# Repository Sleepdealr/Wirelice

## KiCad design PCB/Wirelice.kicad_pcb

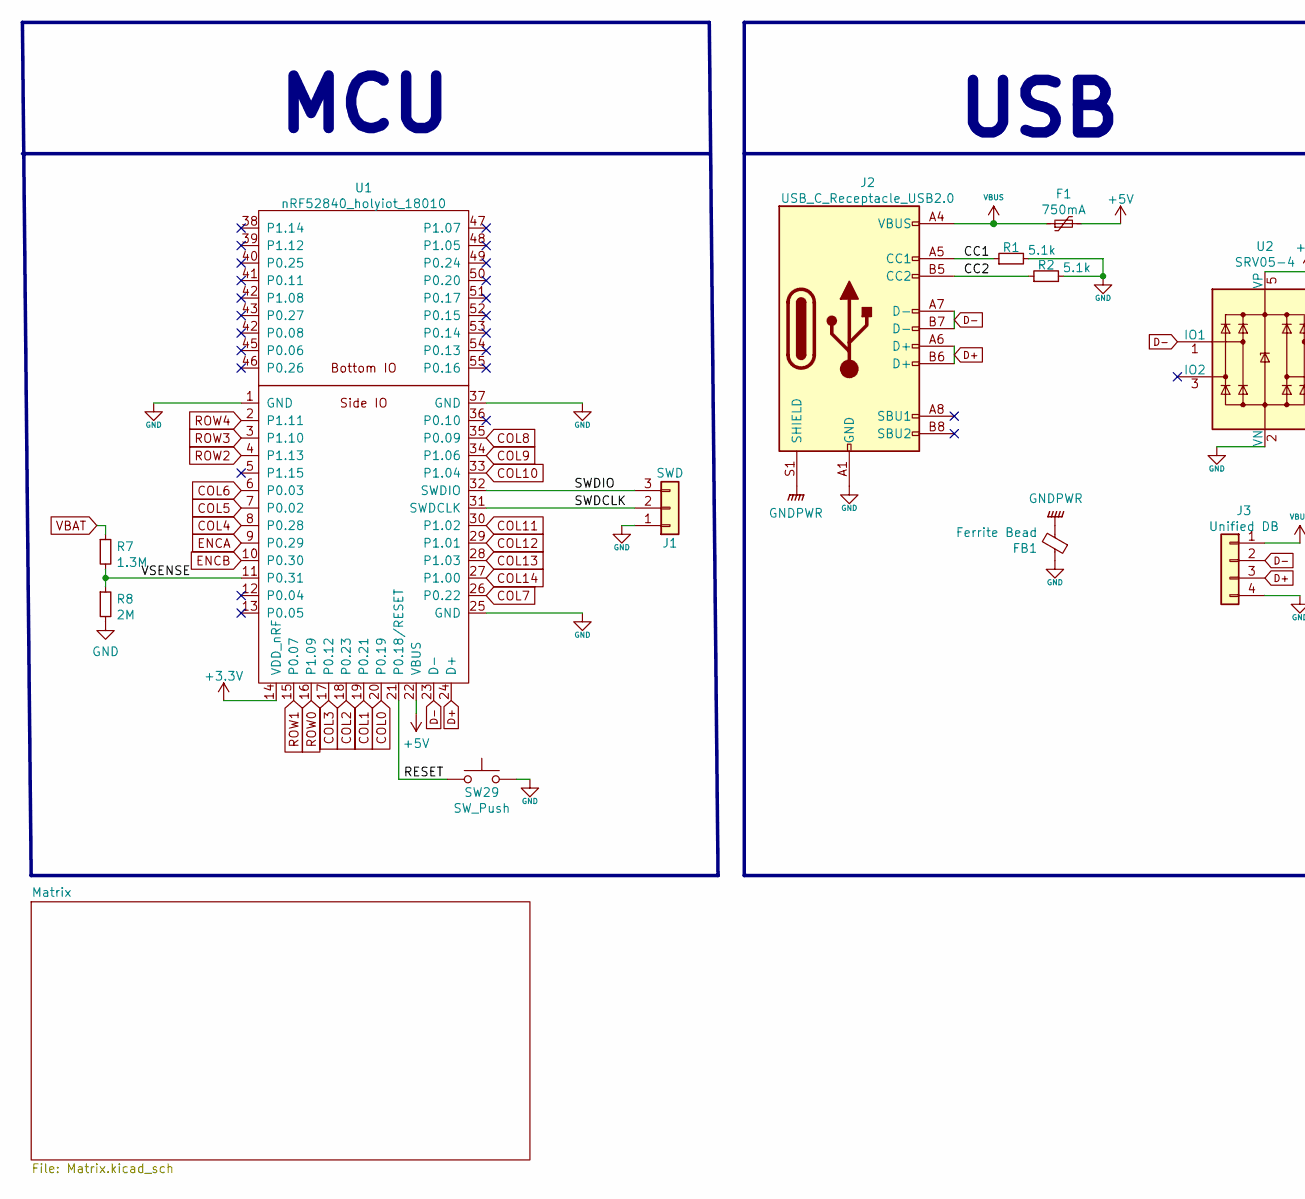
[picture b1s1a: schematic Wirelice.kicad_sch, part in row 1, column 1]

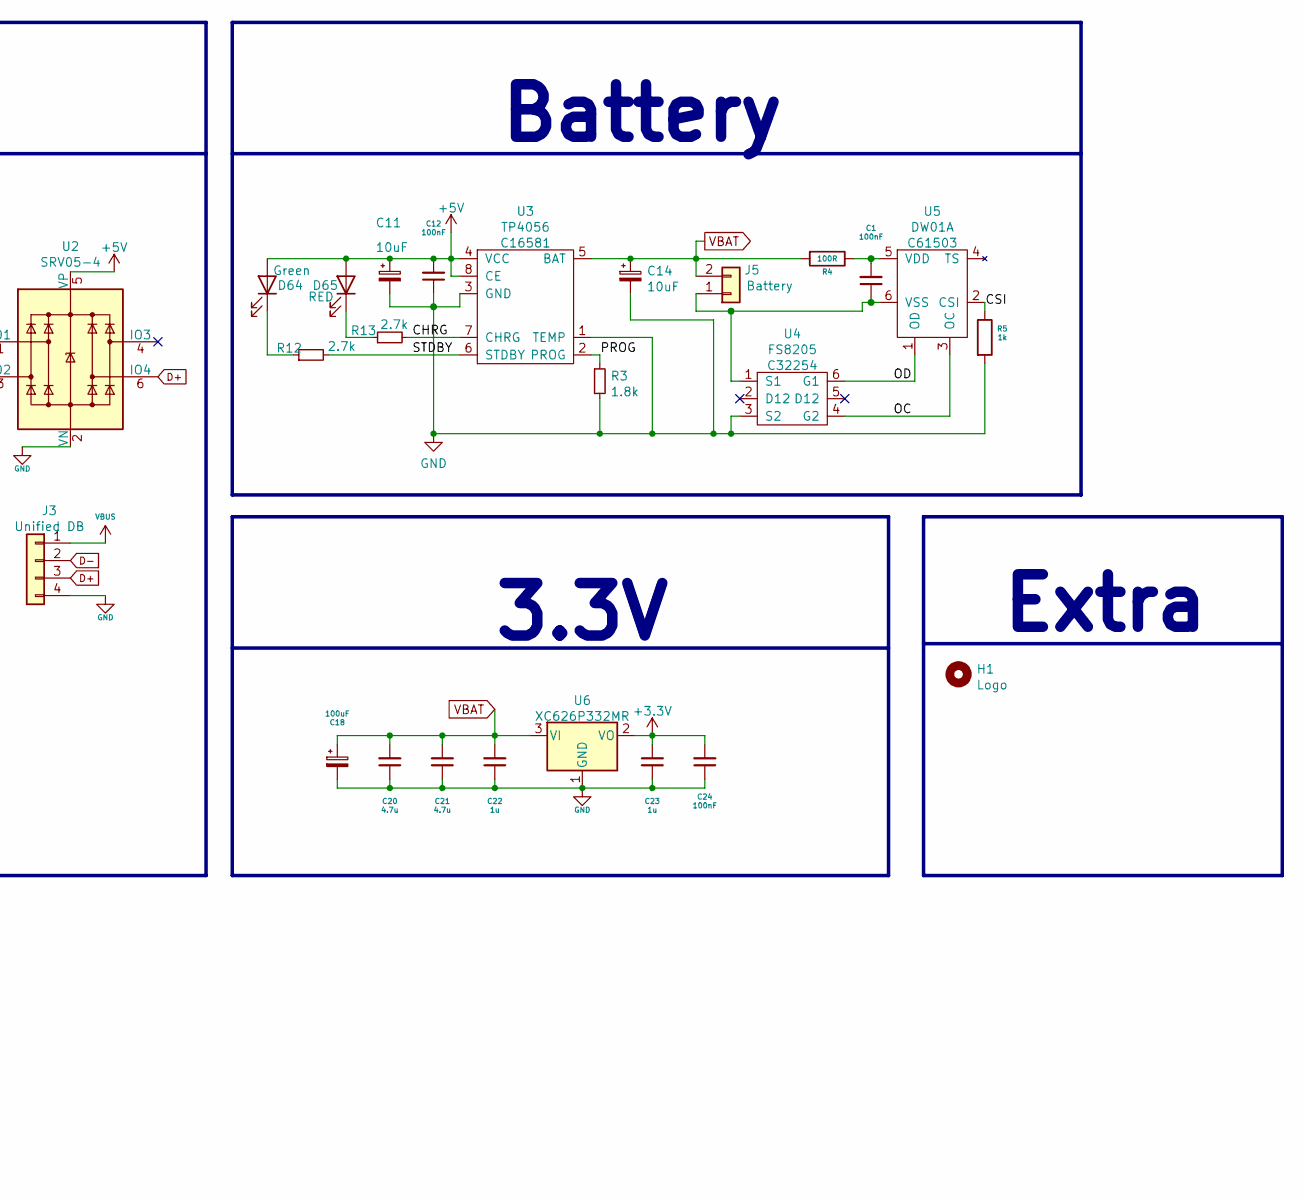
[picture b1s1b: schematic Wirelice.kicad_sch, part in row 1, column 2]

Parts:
C1, C12, C24: 100nF; C_0603_1608Metric; LCSC C14663
C11, C14: 10uF; CP_EIA-3216-18_Kemet-A; LCSC C7171
C18: 100uF; CP_EIA-3528-21_Kemet-B; LCSC C16133
C20, C21: 4.7u; C_0603_1608Metric; LCSC C19666
C22, C23: 1u; C_0603_1608Metric; LCSC C15849
D64: Green; LED_0805_2012Metric; LCSC C2297
D65: RED; LED_0805_2012Metric; LCSC C84256
F1: 750mA; Fuse_0603_1608Metric; LCSC C20792
FB1: Ferrite Bead; L_0805_2012Metric; LCSC C1017
H1: Logo; logo-large-CU
J1: SWD; PinHeader_1x03_P2.54mm_Vertical
J2: USB_C_Receptacle_USB2.0; USB_C_Receptacle_HRO_TYPE-C-31-M-12; LCSC C165948
J3: Unified DB; JST_SH_SM04B-SRSS-TB_1x04-1MP_P1.00mm_Horizontal; Part Number SM04B-SRSS-TB(LF)(SN); LCSC C160404
J5: Battery; JST_PH_S2B-PH-SM4-TB_1x02-1MP_P2.00mm_Horizontal; Part Number S2B-PH-SM4-TB
R1, R2: 5.1k; R_0603_1608Metric; LCSC C23186
R3: 1.8k; R_0603_1608Metric; LCSC C4177
R4: 100R; R_0603_1608Metric; LCSC C22775
R5: 1k; R_0603_1608Metric; LCSC C21190
R7: 1.3M; R_0603_1608Metric; LCSC C170462
R8: 2M; R_0603_1608Metric; LCSC C22976
R12, R13: 2.7k; R_0603_1608Metric; LCSC C13167
SW29: SW_Push; Jumper-UserFriendly
U1: nRF52840_holyiot_18010; nRF52840_holyiot_18010_HS_simple
U2: SRV05-4; SOT-23-6; LCSC C85364
U3: TP4056; SOIC-8-1EP_3.9x4.9mm_P1.27mm_EP2.29x3mm; LCSC C16581
U4: FS8205; SOT-23-6; LCSC C32254
U5: DW01A; SOT-23-6; LCSC C61503
U6: XC626P332MR; SOT-23; LCSC C5446

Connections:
+3V3: C23.2, C24.2, U1.14 (VDD_nRF), U6.2 (VO)
+5V: C11.1, C12.2, D64.2 (A), D65.2 (A), F1.2, U1.22 (VBUS), U2.5 (VP), U3.4 (VCC), U3.8 (CE)
/CC1: J2.A5 (CC1), R1.1
/CC2: J2.B5 (CC2), R2.1
/CHRG: R13.2, U3.7 (CHRG)
/CSI: R5.1, U5.2 (CSI)
/OC: U4.4 (G2), U5.3 (OC)
/OD: U4.6 (G1), U5.1 (OD)
/PROG: R3.1, U3.2 (PROG)
/RESET: SW29.1, U1.21 (P0.18/RESET)
/STDBY: R12.2, U3.6 (STDBY)
/SWDCLK: J1.2, U1.31 (SWDCLK)
/SWDIO: J1.3, U1.32 (SWDIO)
/VSENSE: R7.2, R8.1, U1.11 (P0.31)
COL0: U1.20 (P0.19); also elsewhere on the board
COL1: U1.19 (P0.21); also elsewhere on the board
COL2: U1.18 (P0.23); also elsewhere on the board
COL3: U1.17 (P0.12); also elsewhere on the board
COL4: U1.8 (P0.28); also elsewhere on the board
COL5: U1.7 (P0.02); also elsewhere on the board
COL6: U1.6 (P0.03); also elsewhere on the board
COL7: U1.26 (P0.22); also elsewhere on the board
COL8: U1.35 (P0.09); also elsewhere on the board
COL9: U1.34 (P1.06); also elsewhere on the board
COL10: U1.33 (P1.04); also elsewhere on the board
COL11: U1.30 (P1.02); also elsewhere on the board
COL12: U1.29 (P1.01); also elsewhere on the board
COL13: U1.28 (P1.03); also elsewhere on the board
COL14: U1.27 (P1.00); also elsewhere on the board
D+: J2.A6 (D+), J2.B6 (D+), J3.3, U1.24 (D+), U2.6 (IO4)
D-: J2.A7 (D-), J2.B7 (D-), J3.2, U1.23 (D-), U2.1 (IO1)
ENCA: U1.9 (P0.29); also elsewhere on the board
ENCB: U1.10 (P0.30); also elsewhere on the board
GND: C11.2, C12.1, C14.2, C18.2, C20.1, C21.1, C22.1, C23.1, C24.1, FB1.1, J1.1, J2.A1 (GND), J2.A12 (GND), J2.B1 (GND), J2.B12 (GND), J3.4, R1.2, R2.2, R3.2, R5.2, R8.2, SW29.2, U1.1 (GND), U1.25 (GND), U1.37 (GND), U2.2 (VN), U3.1 (TEMP), U3.3 (GND), U4.3 (S2), U6.1 (GND); also elsewhere on the board
GNDPWR: FB1.2, J2.S1 (SHIELD)
unnamed: C1.1, J5.1, U4.1 (S1), U5.6 (VSS)
unnamed: C1.2, R4.1, U5.5 (VDD)
unnamed: D64.1 (K), R12.1
unnamed: D65.1 (K), R13.1
ROW0: U1.16 (P1.09); also elsewhere on the board
ROW1: U1.15 (P0.07); also elsewhere on the board
ROW2: U1.4 (P1.13); also elsewhere on the board
ROW3: U1.3 (P1.10); also elsewhere on the board
ROW4: U1.2 (P1.11); also elsewhere on the board
VBAT: C14.1, C18.1, C20.2, C21.2, C22.2, J5.2, R4.2, R7.1, U3.5 (BAT), U6.3 (VI)
VBUS: F1.1, J2.A4 (VBUS), J2.A9 (VBUS), J2.B4 (VBUS), J2.B9 (VBUS), J3.1

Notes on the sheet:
MCU
USB
3.3V
Battery
Extra

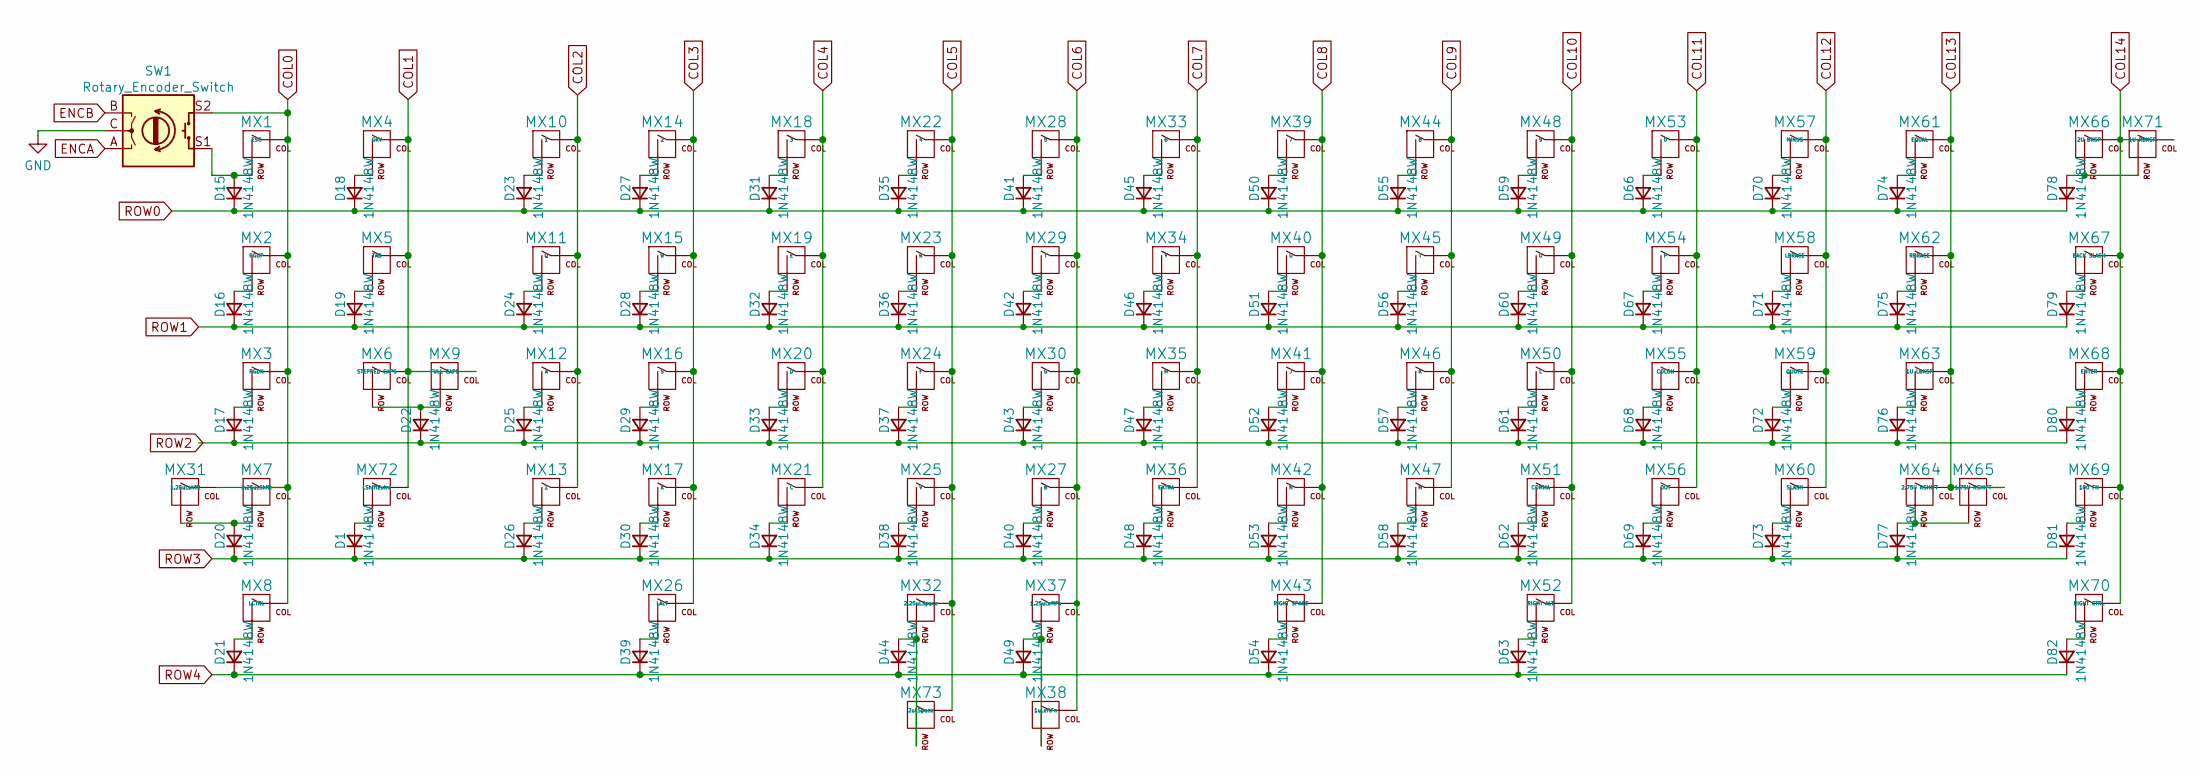
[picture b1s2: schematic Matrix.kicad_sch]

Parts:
D1, D15, D16, D17, D18, D19, D20, D21, D22, D23, D24, D25, D26, D27, D28, D29, D30, D31, D32, D33, D34, D35, D36, D37, D38, D39, D40, D41, D42, D43, D44, D45, D46, D47, D48, D49, D50, D51, D52, D53, D54, D55, D56, D57, D58, D59, D60, D61, D62, D63, D66, D67, D68, D69, D70, D71, D72, D73, D74, D75, D76, D77, D78, D79, D80, D81, D82: 1N4148W; D_SOD-123; LCSC C81598
MX1: ESC; MXOnly-1U-NoLED
MX2: PGUP; MXOnly-1U-NoLED
MX3: PGDN; MXOnly-1U-NoLED
MX4: GRV; MXOnly-1U-NoLED
MX5: TAB; MXOnly-1.5U-NoLED
MX6: STEPPED CAPS; MXOnly-1.25U-NoLED
MX7: 2.25uLShift; MXOnly-2.25U-NoLED
MX8: LCTRL; MXOnly-1.5U-NoLED
MX9: FULL CAPS; MXOnly-1.75U-NoLED
MX10: 1; MXOnly-1U-NoLED
MX11: Q; MXOnly-1U-NoLED
MX12: A; MXOnly-1U-NoLED
MX13: Z; MXOnly-1U-NoLED
MX14: 2; MXOnly-1U-NoLED
MX15: W; MXOnly-1U-NoLED
MX16: S; MXOnly-1U-NoLED
MX17: X; MXOnly-1U-NoLED
MX18: 3; MXOnly-1U-NoLED
MX19: E; MXOnly-1U-NoLED
MX20: D; MXOnly-1U-NoLED
MX21: C; MXOnly-1U-NoLED
MX22: 4; MXOnly-1U-NoLED
MX23: R; MXOnly-1U-NoLED
MX24: F; MXOnly-1U-NoLED
MX25: V; MXOnly-1U-NoLED
MX26: LALT; MXOnly-1.5U-NoLED
MX27: B; MXOnly-1U-NoLED
MX28: 5; MXOnly-1U-NoLED
MX29: T; MXOnly-1U-NoLED
MX30: G; MXOnly-1U-NoLED
MX31: 1.25uLshift; MXOnly-1.25U-NoLED
MX32: 2.25uLSpace; MXOnly-2.25U-ReversedStabilizers-NoLED
MX33: 6; MXOnly-1U-NoLED
MX34: Y; MXOnly-1U-NoLED
MX35: H; MXOnly-1U-NoLED
MX36: EXTRA; MXOnly-1U-NoLED
MX37: 1.25uLeftFn; MXOnly-1.25U-NoLED
MX38: 1uLeftFn; MXOnly-1U-NoLED
MX39: 7; MXOnly-1U-NoLED
MX40: U; MXOnly-1U-NoLED
MX41: J; MXOnly-1U-NoLED
MX42: N; MXOnly-1U-NoLED
MX43: RIGHT SPACE; MXOnly-2.75U-ReversedStabilizers-NoLED
MX44: 8; MXOnly-1U-NoLED
MX45: I; MXOnly-1U-NoLED
MX46: K; MXOnly-1U-NoLED
MX47: M; MXOnly-1U-NoLED
MX48: 9; MXOnly-1U-NoLED
MX49: O; MXOnly-1U-NoLED
MX50: L; MXOnly-1U-NoLED
MX51: COMMA; MXOnly-1U-NoLED
MX52: RIGHT ALT; MXOnly-1.5U-NoLED
MX53: 0; MXOnly-1U-NoLED
MX54: P; MXOnly-1U-NoLED
MX55: COLON; MXOnly-1U-NoLED
MX56: DOT; MXOnly-1U-NoLED
MX57: MINUS; MXOnly-1U-NoLED
MX58: LBRACE; MXOnly-1U-NoLED
MX59: QUOTE; MXOnly-1U-NoLED
MX60: SLASH; MXOnly-1U-NoLED
MX61: EQUAL; MXOnly-1U-NoLED
MX62: RBRACE; MXOnly-1U-NoLED
MX63: 1U LBKSP; MXOnly-1U-NoLED
MX64: 2.75U RSHIFT; MXOnly-2.75U-NoLED
MX65: 1.75U RSHIFT; MXOnly-1.75U-NoLED
MX66: 2U BKSP; MXOnly-2U-NoLED
MX67: BACK SLASH; MXOnly-1.5U-NoLED
MX68: ENTER; MXOnly-2.25U-ReversedStabilizers-NoLED
MX69: 100 FN; MXOnly-1U-NoLED
MX70: RIGHT CTRL; MXOnly-1.5U-NoLED
MX71: 1U RBKSP; MXOnly-1U-NoLED
MX72: LShiftExtra; MXOnly-1U-NoLED
MX73: 2uLSpace; MXOnly-2U-ReversedStabilizers-NoLED
SW1: Rotary_Encoder_Switch; RotaryEncoder_Alps_EC11E-Switch_Vertical_H20mm

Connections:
COL0: MX1.1 (COL), MX2.1 (COL), MX3.1 (COL), MX7.1 (COL), MX8.1 (COL), MX31.1 (COL), SW1.S2; also elsewhere on the board
COL1: MX4.1 (COL), MX5.1 (COL), MX6.1 (COL), MX9.1 (COL), MX72.1 (COL); also elsewhere on the board
COL2: MX10.1 (COL), MX11.1 (COL), MX12.1 (COL), MX13.1 (COL); also elsewhere on the board
COL3: MX14.1 (COL), MX15.1 (COL), MX16.1 (COL), MX17.1 (COL), MX26.1 (COL); also elsewhere on the board
COL4: MX18.1 (COL), MX19.1 (COL), MX20.1 (COL), MX21.1 (COL); also elsewhere on the board
COL5: MX22.1 (COL), MX23.1 (COL), MX24.1 (COL), MX25.1 (COL), MX32.1 (COL), MX73.1 (COL); also elsewhere on the board
COL6: MX27.1 (COL), MX28.1 (COL), MX29.1 (COL), MX30.1 (COL), MX37.1 (COL), MX38.1 (COL); also elsewhere on the board
COL7: MX33.1 (COL), MX34.1 (COL), MX35.1 (COL), MX36.1 (COL); also elsewhere on the board
COL8: MX39.1 (COL), MX40.1 (COL), MX41.1 (COL), MX42.1 (COL), MX43.1 (COL); also elsewhere on the board
COL9: MX44.1 (COL), MX45.1 (COL), MX46.1 (COL), MX47.1 (COL); also elsewhere on the board
COL10: MX48.1 (COL), MX49.1 (COL), MX50.1 (COL), MX51.1 (COL), MX52.1 (COL); also elsewhere on the board
COL11: MX53.1 (COL), MX54.1 (COL), MX55.1 (COL), MX56.1 (COL); also elsewhere on the board
COL12: MX57.1 (COL), MX58.1 (COL), MX59.1 (COL), MX60.1 (COL); also elsewhere on the board
COL13: MX61.1 (COL), MX62.1 (COL), MX63.1 (COL), MX64.1 (COL), MX65.1 (COL); also elsewhere on the board
COL14: MX66.1 (COL), MX67.1 (COL), MX68.1 (COL), MX69.1 (COL), MX70.1 (COL), MX71.1 (COL); also elsewhere on the board
ENCA: SW1.A; also elsewhere on the board
ENCB: SW1.B; also elsewhere on the board
GND: SW1.C; also elsewhere on the board
unnamed: D1.2 (A), MX72.2 (ROW)
unnamed: D15.2 (A), MX1.2 (ROW), SW1.S1
unnamed: D16.2 (A), MX2.2 (ROW)
unnamed: D17.2 (A), MX3.2 (ROW)
unnamed: D18.2 (A), MX4.2 (ROW)
unnamed: D19.2 (A), MX5.2 (ROW)
unnamed: D20.2 (A), MX7.2 (ROW), MX31.2 (ROW)
unnamed: D21.2 (A), MX8.2 (ROW)
unnamed: D22.2 (A), MX6.2 (ROW), MX9.2 (ROW)
unnamed: D23.2 (A), MX10.2 (ROW)
unnamed: D24.2 (A), MX11.2 (ROW)
unnamed: D25.2 (A), MX12.2 (ROW)
unnamed: D26.2 (A), MX13.2 (ROW)
unnamed: D27.2 (A), MX14.2 (ROW)
unnamed: D28.2 (A), MX15.2 (ROW)
unnamed: D29.2 (A), MX16.2 (ROW)
unnamed: D30.2 (A), MX17.2 (ROW)
unnamed: D31.2 (A), MX18.2 (ROW)
unnamed: D32.2 (A), MX19.2 (ROW)
unnamed: D33.2 (A), MX20.2 (ROW)
unnamed: D34.2 (A), MX21.2 (ROW)
unnamed: D35.2 (A), MX22.2 (ROW)
unnamed: D36.2 (A), MX23.2 (ROW)
unnamed: D37.2 (A), MX24.2 (ROW)
unnamed: D38.2 (A), MX25.2 (ROW)
unnamed: D39.2 (A), MX26.2 (ROW)
unnamed: D40.2 (A), MX27.2 (ROW)
unnamed: D41.2 (A), MX28.2 (ROW)
unnamed: D42.2 (A), MX29.2 (ROW)
unnamed: D43.2 (A), MX30.2 (ROW)
unnamed: D44.2 (A), MX32.2 (ROW), MX73.2 (ROW)
unnamed: D45.2 (A), MX33.2 (ROW)
unnamed: D46.2 (A), MX34.2 (ROW)
unnamed: D47.2 (A), MX35.2 (ROW)
unnamed: D48.2 (A), MX36.2 (ROW)
unnamed: D49.2 (A), MX37.2 (ROW), MX38.2 (ROW)
unnamed: D50.2 (A), MX39.2 (ROW)
unnamed: D51.2 (A), MX40.2 (ROW)
unnamed: D52.2 (A), MX41.2 (ROW)
unnamed: D53.2 (A), MX42.2 (ROW)
unnamed: D54.2 (A), MX43.2 (ROW)
unnamed: D55.2 (A), MX44.2 (ROW)
unnamed: D56.2 (A), MX45.2 (ROW)
unnamed: D57.2 (A), MX46.2 (ROW)
unnamed: D58.2 (A), MX47.2 (ROW)
unnamed: D59.2 (A), MX48.2 (ROW)
unnamed: D60.2 (A), MX49.2 (ROW)
unnamed: D61.2 (A), MX50.2 (ROW)
unnamed: D62.2 (A), MX51.2 (ROW)
unnamed: D63.2 (A), MX52.2 (ROW)
unnamed: D66.2 (A), MX53.2 (ROW)
unnamed: D67.2 (A), MX54.2 (ROW)
unnamed: D68.2 (A), MX55.2 (ROW)
unnamed: D69.2 (A), MX56.2 (ROW)
unnamed: D70.2 (A), MX57.2 (ROW)
unnamed: D71.2 (A), MX58.2 (ROW)
unnamed: D72.2 (A), MX59.2 (ROW)
unnamed: D73.2 (A), MX60.2 (ROW)
unnamed: D74.2 (A), MX61.2 (ROW)
unnamed: D75.2 (A), MX62.2 (ROW)
unnamed: D76.2 (A), MX63.2 (ROW)
unnamed: D77.2 (A), MX64.2 (ROW), MX65.2 (ROW)
unnamed: D78.2 (A), MX66.2 (ROW), MX71.2 (ROW)
unnamed: D79.2 (A), MX67.2 (ROW)
unnamed: D80.2 (A), MX68.2 (ROW)
unnamed: D81.2 (A), MX69.2 (ROW)
unnamed: D82.2 (A), MX70.2 (ROW)
ROW0: D15.1 (K), D18.1 (K), D23.1 (K), D27.1 (K), D31.1 (K), D35.1 (K), D41.1 (K), D45.1 (K), D50.1 (K), D55.1 (K), D59.1 (K), D66.1 (K), D70.1 (K), D74.1 (K), D78.1 (K); also elsewhere on the board
ROW1: D16.1 (K), D19.1 (K), D24.1 (K), D28.1 (K), D32.1 (K), D36.1 (K), D42.1 (K), D46.1 (K), D51.1 (K), D56.1 (K), D60.1 (K), D67.1 (K), D71.1 (K), D75.1 (K), D79.1 (K); also elsewhere on the board
ROW2: D17.1 (K), D22.1 (K), D25.1 (K), D29.1 (K), D33.1 (K), D37.1 (K), D43.1 (K), D47.1 (K), D52.1 (K), D57.1 (K), D61.1 (K), D68.1 (K), D72.1 (K), D76.1 (K), D80.1 (K); also elsewhere on the board
ROW3: D1.1 (K), D20.1 (K), D26.1 (K), D30.1 (K), D34.1 (K), D38.1 (K), D40.1 (K), D48.1 (K), D53.1 (K), D58.1 (K), D62.1 (K), D69.1 (K), D73.1 (K), D77.1 (K), D81.1 (K); also elsewhere on the board
ROW4: D21.1 (K), D39.1 (K), D44.1 (K), D49.1 (K), D54.1 (K), D63.1 (K), D82.1 (K); also elsewhere on the board

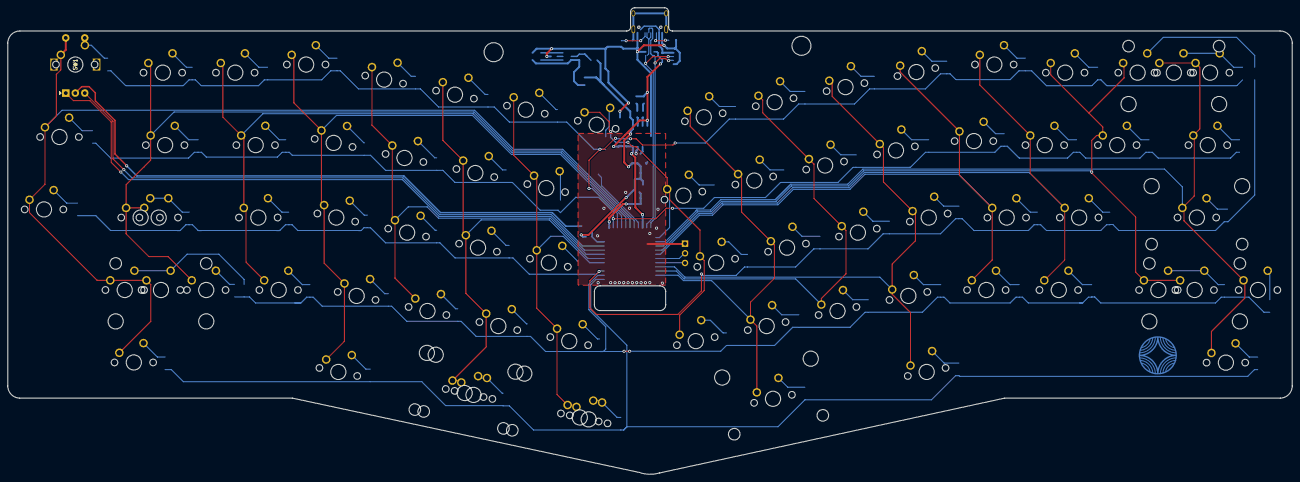
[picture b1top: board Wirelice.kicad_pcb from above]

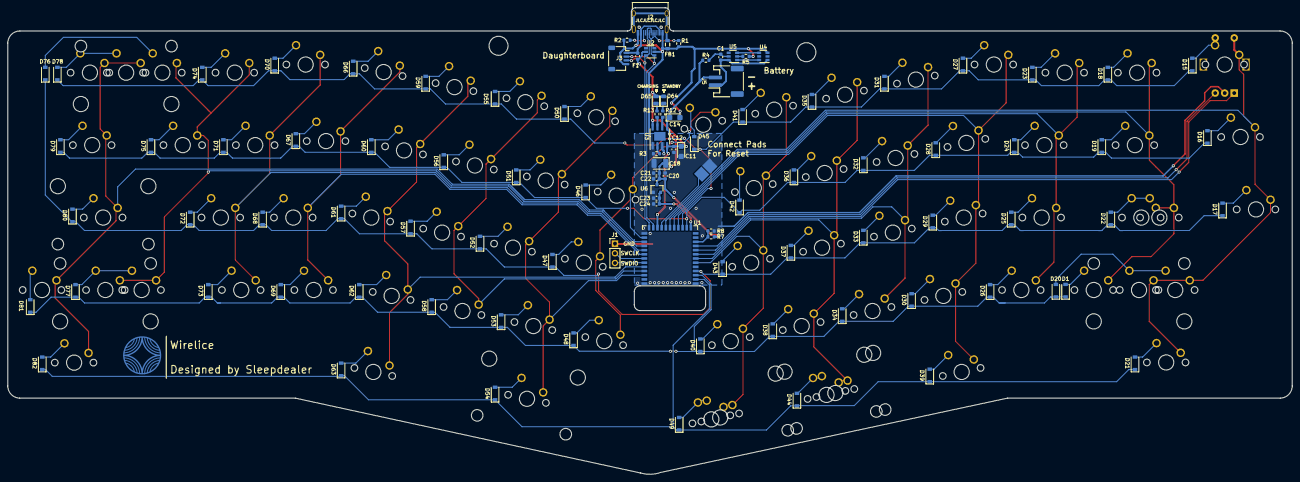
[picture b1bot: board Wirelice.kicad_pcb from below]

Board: 2 copper layers, 337.7 x 122.7 mm, 176 parts (102 on the bottom side), 113 nets.

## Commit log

2021-04-30 Removed LEDS and updated holes
2021-04-30 Compacted components and removed RGBs
2021-07-01 Updated things
2021-07-01 Moved to separate folders
2021-07-02 Add Plate and Back
2021-07-02 Update top offset
2021-07-10 Updated stuff
2021-07-17 Update clearances
